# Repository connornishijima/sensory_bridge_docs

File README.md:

**This is a work-in-progress consolidation of the Sensory Bridge tools and documentation hosted entirely by GitHub Pages!**

*Access the site here:*

https://connornishijima.github.io/sensory_bridge_docs/

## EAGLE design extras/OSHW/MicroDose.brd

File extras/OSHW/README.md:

## OSHW Files for MicroDose LED Strips

More info here:
https://sensorybridge.rocks/hardware.html

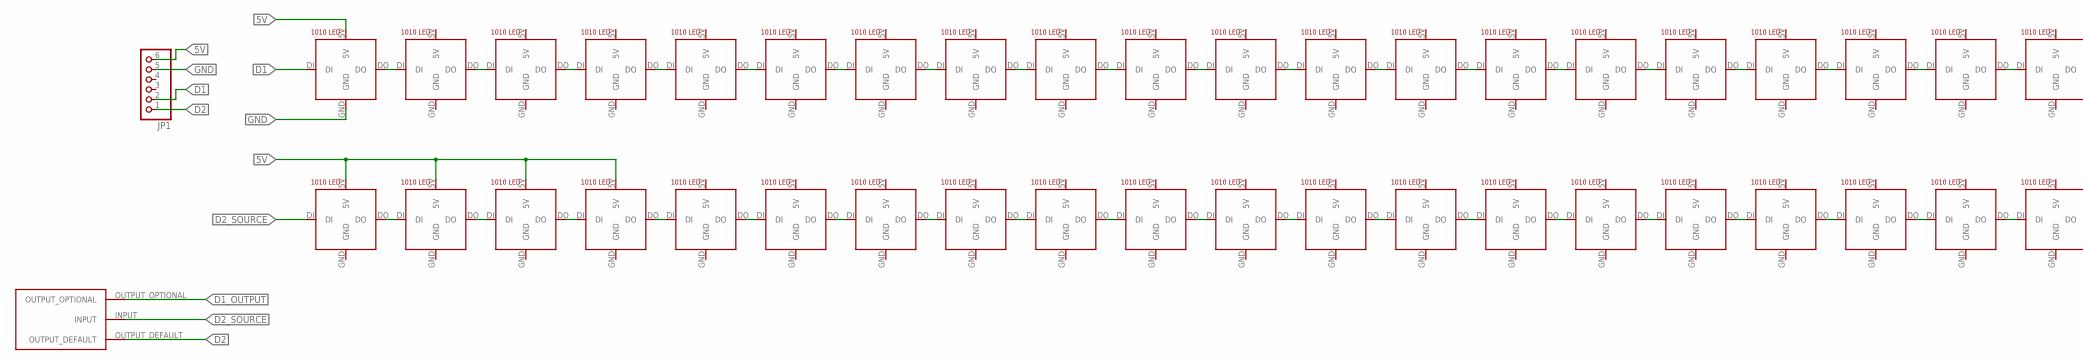
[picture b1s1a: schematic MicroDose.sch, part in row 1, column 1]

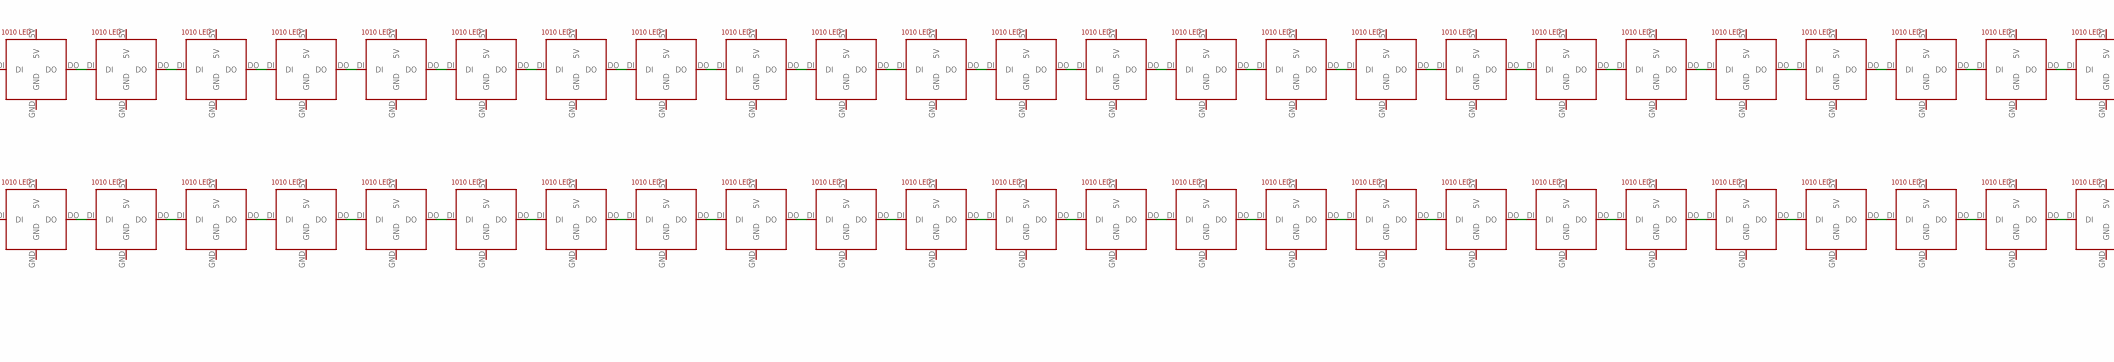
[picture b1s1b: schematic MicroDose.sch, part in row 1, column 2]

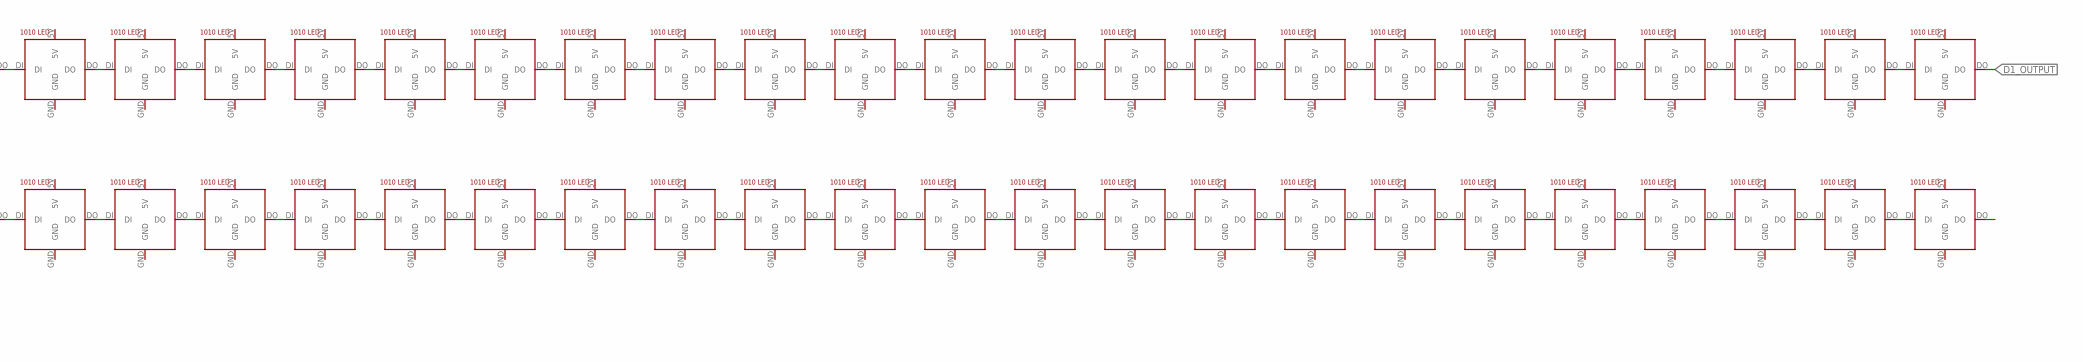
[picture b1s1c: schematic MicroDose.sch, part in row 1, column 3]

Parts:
JP1: PINHD-1X6/90; 1X06/90
U$1, U$2, U$3, U$4, U$5, U$6, U$7, U$8, U$9, U$10, U$11, U$12, U$13, U$14, U$15, U$16, U$17, U$18, U$19, U$20, U$21, U$22, U$23, U$24, U$25, U$26, U$27, U$28, U$29, U$30, U$31, U$32, U$33, U$34, U$35, U$36, U$37, U$38, U$39, U$40, U$41, U$42, U$43, U$44, U$45, U$46, U$47, U$48, U$49, U$50, U$51, U$52, U$53, U$54, U$55, U$56, U$57, U$58, U$59, U$60, U$61, U$62, U$63, U$64, U$65, U$66, U$67, U$68, U$69, U$70, U$71, U$72, U$73, U$74, U$75, U$76, U$77, U$78, U$79, U$80, U$81, U$82, U$83, U$84, U$85, U$86, U$87, U$88, U$89, U$90, U$91, U$92, U$93, U$94, U$95, U$96, U$97, U$98, U$99, U$100, U$101, U$102, U$103, U$104, U$105, U$106, U$107, U$108, U$109, U$110, U$111, U$112, U$113, U$114, U$115, U$116, U$117, U$118, U$119, U$120, U$121, U$122, U$123, U$124, U$125, U$126, U$127, U$128: 1010_LED
U$129: SOLDER_JUMPER

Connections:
5V: JP1.6, U$1.5V, U$2.5V, U$3.5V, U$4.5V, U$5.5V, U$6.5V, U$7.5V, U$8.5V, U$9.5V, U$10.5V, U$11.5V, U$12.5V, U$13.5V, U$14.5V, U$15.5V, U$16.5V, U$17.5V, U$18.5V, U$19.5V, U$20.5V, U$21.5V, U$22.5V, U$23.5V, U$24.5V, U$25.5V, U$26.5V, U$27.5V, U$28.5V, U$29.5V, U$30.5V, U$31.5V, U$32.5V, U$33.5V, U$34.5V, U$35.5V, U$36.5V, U$37.5V, U$38.5V, U$39.5V, U$40.5V, U$41.5V, U$42.5V, U$43.5V, U$44.5V, U$45.5V, U$46.5V, U$47.5V, U$48.5V, U$49.5V, U$50.5V, U$51.5V, U$52.5V, U$53.5V, U$54.5V, U$55.5V, U$56.5V, U$57.5V, U$58.5V, U$59.5V, U$60.5V, U$61.5V, U$62.5V, U$63.5V, U$64.5V, U$65.5V, U$66.5V, U$67.5V, U$68.5V, U$69.5V, U$70.5V, U$71.5V, U$72.5V, U$73.5V, U$74.5V, U$75.5V, U$76.5V, U$77.5V, U$78.5V, U$79.5V, U$80.5V, U$81.5V, U$82.5V, U$83.5V, U$84.5V, U$85.5V, U$86.5V, U$87.5V, U$88.5V, U$89.5V, U$90.5V, U$91.5V, U$92.5V, U$93.5V, U$94.5V, U$95.5V, U$96.5V, U$97.5V, U$98.5V, U$99.5V, U$100.5V, U$101.5V, U$102.5V, U$103.5V, U$104.5V, U$105.5V, U$106.5V, U$107.5V, U$108.5V, U$109.5V, U$110.5V, U$111.5V, U$112.5V, U$113.5V, U$114.5V, U$115.5V, U$116.5V, U$117.5V, U$118.5V, U$119.5V, U$120.5V, U$121.5V, U$122.5V, U$123.5V, U$124.5V, U$125.5V, U$126.5V, U$127.5V, U$128.5V
D1: JP1.2, U$1.DI
D1_OUTPUT: U$64.DO, U$129.OUTPUT_OPTIONAL
D2: JP1.1, U$129.OUTPUT_DEFAULT
D2_SOURCE: U$65.DI, U$129.INPUT
GND: JP1.5, U$1.GND, U$2.GND, U$3.GND, U$4.GND, U$5.GND, U$6.GND, U$7.GND, U$8.GND, U$9.GND, U$10.GND, U$11.GND, U$12.GND, U$13.GND, U$14.GND, U$15.GND, U$16.GND, U$17.GND, U$18.GND, U$19.GND, U$20.GND, U$21.GND, U$22.GND, U$23.GND, U$24.GND, U$25.GND, U$26.GND, U$27.GND, U$28.GND, U$29.GND, U$30.GND, U$31.GND, U$32.GND, U$33.GND, U$34.GND, U$35.GND, U$36.GND, U$37.GND, U$38.GND, U$39.GND, U$40.GND, U$41.GND, U$42.GND, U$43.GND, U$44.GND, U$45.GND, U$46.GND, U$47.GND, U$48.GND, U$49.GND, U$50.GND, U$51.GND, U$52.GND, U$53.GND, U$54.GND, U$55.GND, U$56.GND, U$57.GND, U$58.GND, U$59.GND, U$60.GND, U$61.GND, U$62.GND, U$63.GND, U$64.GND, U$65.GND, U$66.GND, U$67.GND, U$68.GND, U$69.GND, U$70.GND, U$71.GND, U$72.GND, U$73.GND, U$74.GND, U$75.GND, U$76.GND, U$77.GND, U$78.GND, U$79.GND, U$80.GND, U$81.GND, U$82.GND, U$83.GND, U$84.GND, U$85.GND, U$86.GND, U$87.GND, U$88.GND, U$89.GND, U$90.GND, U$91.GND, U$92.GND, U$93.GND, U$94.GND, U$95.GND, U$96.GND, U$97.GND, U$98.GND, U$99.GND, U$100.GND, U$101.GND, U$102.GND, U$103.GND, U$104.GND, U$105.GND, U$106.GND, U$107.GND, U$108.GND, U$109.GND, U$110.GND, U$111.GND, U$112.GND, U$113.GND, U$114.GND, U$115.GND, U$116.GND, U$117.GND, U$118.GND, U$119.GND, U$120.GND, U$121.GND, U$122.GND, U$123.GND, U$124.GND, U$125.GND, U$126.GND, U$127.GND, U$128.GND
unnamed: U$1.DO, U$2.DI
unnamed: U$2.DO, U$3.DI
unnamed: U$3.DO, U$4.DI
unnamed: U$4.DO, U$5.DI
unnamed: U$5.DO, U$6.DI
unnamed: U$6.DO, U$7.DI
unnamed: U$7.DO, U$8.DI
unnamed: U$8.DO, U$9.DI
unnamed: U$9.DO, U$10.DI
unnamed: U$10.DO, U$11.DI
unnamed: U$11.DO, U$12.DI
unnamed: U$12.DO, U$13.DI
unnamed: U$13.DO, U$14.DI
unnamed: U$14.DO, U$15.DI
unnamed: U$15.DO, U$16.DI
unnamed: U$16.DO, U$17.DI
unnamed: U$17.DO, U$18.DI
unnamed: U$18.DO, U$19.DI
unnamed: U$19.DO, U$20.DI
unnamed: U$20.DO, U$21.DI
unnamed: U$21.DO, U$22.DI
unnamed: U$22.DO, U$23.DI
unnamed: U$23.DO, U$24.DI
unnamed: U$24.DO, U$25.DI
unnamed: U$25.DO, U$26.DI
unnamed: U$26.DO, U$27.DI
unnamed: U$27.DO, U$28.DI
unnamed: U$28.DO, U$29.DI
unnamed: U$29.DO, U$30.DI
unnamed: U$30.DO, U$31.DI
unnamed: U$31.DO, U$32.DI
unnamed: U$32.DO, U$33.DI
unnamed: U$33.DO, U$34.DI
unnamed: U$34.DO, U$35.DI
unnamed: U$35.DO, U$36.DI
unnamed: U$36.DO, U$37.DI
unnamed: U$37.DO, U$38.DI
unnamed: U$38.DO, U$39.DI
unnamed: U$39.DO, U$40.DI
unnamed: U$40.DO, U$41.DI
unnamed: U$41.DO, U$42.DI
unnamed: U$42.DO, U$43.DI
unnamed: U$43.DO, U$44.DI
unnamed: U$44.DO, U$45.DI
unnamed: U$45.DO, U$46.DI
unnamed: U$46.DO, U$47.DI
unnamed: U$47.DO, U$48.DI
unnamed: U$48.DO, U$49.DI
unnamed: U$49.DO, U$50.DI
unnamed: U$50.DO, U$51.DI
unnamed: U$51.DO, U$52.DI
unnamed: U$52.DO, U$53.DI
unnamed: U$53.DO, U$54.DI
unnamed: U$54.DO, U$55.DI
unnamed: U$55.DO, U$56.DI
unnamed: U$56.DO, U$57.DI
unnamed: U$57.DO, U$58.DI
unnamed: U$58.DO, U$59.DI
unnamed: U$59.DO, U$60.DI
unnamed: U$60.DO, U$61.DI
unnamed: U$61.DO, U$62.DI
unnamed: U$62.DO, U$63.DI
unnamed: U$63.DO, U$64.DI
unnamed: U$65.DO, U$66.DI
unnamed: U$66.DO, U$67.DI
unnamed: U$67.DO, U$68.DI
unnamed: U$68.DO, U$69.DI
unnamed: U$69.DO, U$70.DI
unnamed: U$70.DO, U$71.DI
unnamed: U$71.DO, U$72.DI
unnamed: U$72.DO, U$73.DI
unnamed: U$73.DO, U$74.DI
unnamed: U$74.DO, U$75.DI
unnamed: U$75.DO, U$76.DI
unnamed: U$76.DO, U$77.DI
unnamed: U$77.DO, U$78.DI
unnamed: U$78.DO, U$79.DI
unnamed: U$79.DO, U$80.DI
unnamed: U$80.DO, U$81.DI
unnamed: U$81.DO, U$82.DI
unnamed: U$82.DO, U$83.DI
unnamed: U$83.DO, U$84.DI
unnamed: U$84.DO, U$85.DI
unnamed: U$85.DO, U$86.DI
unnamed: U$86.DO, U$87.DI
unnamed: U$87.DO, U$88.DI
unnamed: U$88.DO, U$89.DI
unnamed: U$89.DO, U$90.DI
unnamed: U$90.DO, U$91.DI
unnamed: U$91.DO, U$92.DI
unnamed: U$92.DO, U$93.DI
unnamed: U$93.DO, U$94.DI
unnamed: U$94.DO, U$95.DI
unnamed: U$95.DO, U$96.DI
unnamed: U$96.DO, U$97.DI
unnamed: U$97.DO, U$98.DI
unnamed: U$98.DO, U$99.DI
unnamed: U$99.DO, U$100.DI
unnamed: U$100.DO, U$101.DI
unnamed: U$101.DO, U$102.DI
unnamed: U$102.DO, U$103.DI
unnamed: U$103.DO, U$104.DI
unnamed: U$104.DO, U$105.DI
unnamed: U$105.DO, U$106.DI
unnamed: U$106.DO, U$107.DI
unnamed: U$107.DO, U$108.DI
unnamed: U$108.DO, U$109.DI
unnamed: U$109.DO, U$110.DI
unnamed: U$110.DO, U$111.DI
unnamed: U$111.DO, U$112.DI
unnamed: U$112.DO, U$113.DI
unnamed: U$113.DO, U$114.DI
unnamed: U$114.DO, U$115.DI
unnamed: U$115.DO, U$116.DI
unnamed: U$116.DO, U$117.DI
unnamed: U$117.DO, U$118.DI
unnamed: U$118.DO, U$119.DI
unnamed: U$119.DO, U$120.DI
unnamed: U$120.DO, U$121.DI
unnamed: U$121.DO, U$122.DI
unnamed: U$122.DO, U$123.DI
unnamed: U$123.DO, U$124.DI
unnamed: U$124.DO, U$125.DI
unnamed: U$125.DO, U$126.DI
unnamed: U$126.DO, U$127.DI
unnamed: U$127.DO, U$128.DI

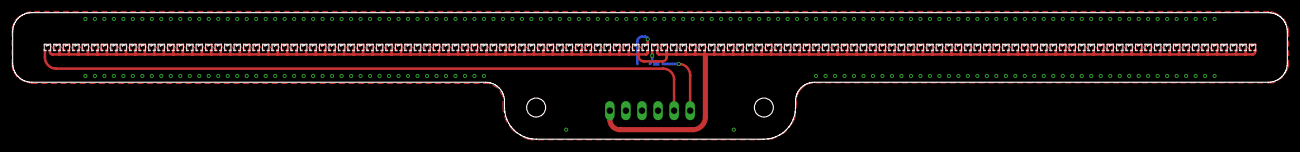
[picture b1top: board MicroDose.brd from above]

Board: 2 copper layers, 201.5 x 20.0 mm, 130 parts (1 on the bottom side), 132 nets.

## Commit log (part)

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2023-12-06 [ImgBot] Optimize images
    *Total -- 2,218.91kb -> 2,062.32kb (7.06%)
    /img/settings_page_pic.png -- 377.04kb -> 323.19kb (14.28%)
    /img/2.jpg -- 239.88kb -> 218.03kb (9.11%)
    /img/mast_insert.png -- 179.07kb -> 168.11kb (6.12%)
    /img/5.jpg -- 174.00kb -> 163.66kb (5.94%)
    /img/7.jpg -- 152.09kb -> 143.71kb (5.51%)
2023-12-07 Create troubleshooting
2023-12-07 Rename troubleshooting to troubleshooting_file
2023-12-08 Rename index.md to index_old.md
2023-12-28 Bump jekyll from 4.3.2 to 4.3.3
    Bumps [jekyll](https://github.com/jekyll/jekyll) from 4.3.2 to 4.3.3.
    - [Release notes](https://github.com/jekyll/jekyll/releases)
    - [Changelog](https://github.com/jekyll/jekyll/blob/master/History.markdown)
    - [Commits](https://github.com/jekyll/jekyll/compare/v4.3.2...v4.3.3)
    ---
    updated-dependencies:
2024-01-13 [ImgBot] Optimize images
    *Total -- 42,892.13kb -> 39,856.36kb (7.08%)
    /img/mood.svg -- 1.19kb -> 0.77kb (34.95%)
    /img/chroma.svg -- 1.35kb -> 0.96kb (28.66%)
    /img/anatomy.jpg -- 3,672.83kb -> 2,626.25kb (28.5%)
    /img/photons.svg -- 1.17kb -> 0.86kb (27.02%)
    /img/mode.svg -- 1.76kb -> 1.41kb (19.63%)
2024-02-23 Bump just-the-docs from 0.7.0 to 0.8.0
    Bumps [just-the-docs](https://github.com/just-the-docs/just-the-docs) from 0.7.0 to 0.8.0.
    - [Release notes](https://github.com/just-the-docs/just-the-docs/releases)
    - [Changelog](https://github.com/just-the-docs/just-the-docs/blob/main/CHANGELOG.md)
    - [Commits](https://github.com/just-the-docs/just-the-docs/compare/v0.7.0...v0.8.0)
    ---
    updated-dependencies:
2024-03-07 Bump just-the-docs from 0.7.0 to 0.8.1
    Bumps [just-the-docs](https://github.com/just-the-docs/just-the-docs) from 0.7.0 to 0.8.1.
    - [Release notes](https://github.com/just-the-docs/just-the-docs/releases)
    - [Changelog](https://github.com/just-the-docs/just-the-docs/blob/main/CHANGELOG.md)
    - [Commits](https://github.com/just-the-docs/just-the-docs/compare/v0.7.0...v0.8.1)
    ---
    updated-dependencies:
